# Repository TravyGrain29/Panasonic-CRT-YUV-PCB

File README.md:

# Panasonic-CRT-YUV-PCB
## DISCLAIMER
I'm not a professional, this was a side project I completed for fun. I cannot guarantee compatibility with your model CRT. I am not responsible for any damage or harm you may inflict upon yourself or your devices. Working on CRTs is very dangerous and should only be done by individuals with the required knowledge and experience. Do not attempt this project if you are a novice with electronics or CRTs.

## Overview

### CRT Specs
Model: Panasonic Tau TC-21PM50A

Chassis: GP3

UOC IC/Jungle: TDA9590N48AX

### What is this?
This is a PCB I designed, based off exisiting Panasonic schematics, that allows Panasonic Tau CRTs using the GP3 chassis to accept component (YPbPr) video input. This is intended for use with GP3 CRTs that lack native component or RGB inputs. The board converts incoming YPbPr signals from an external device into sigals that the video processor can understand and display properly. Without this PCB, the video will not display correctly and will appear distorted.

### How does it work?
Panasonic CRTs that utilise the GP3 chassis but lack component input, still have the basic foundations present that allow us to provide our own component input. This is due to Panasonic reusing the same chassis and processors between higher end and lower end models. All that was required for this mod was to unlock component input as an AV option via the service menu and then installing the missing hardware and connections. This board replaces the missing YUV circuit board that came with component enabled models, allowing us to build the YUV input path ourselves.

### How can I build this?
A written guide will be provided in PDF format with instructions on how to perform the modification.

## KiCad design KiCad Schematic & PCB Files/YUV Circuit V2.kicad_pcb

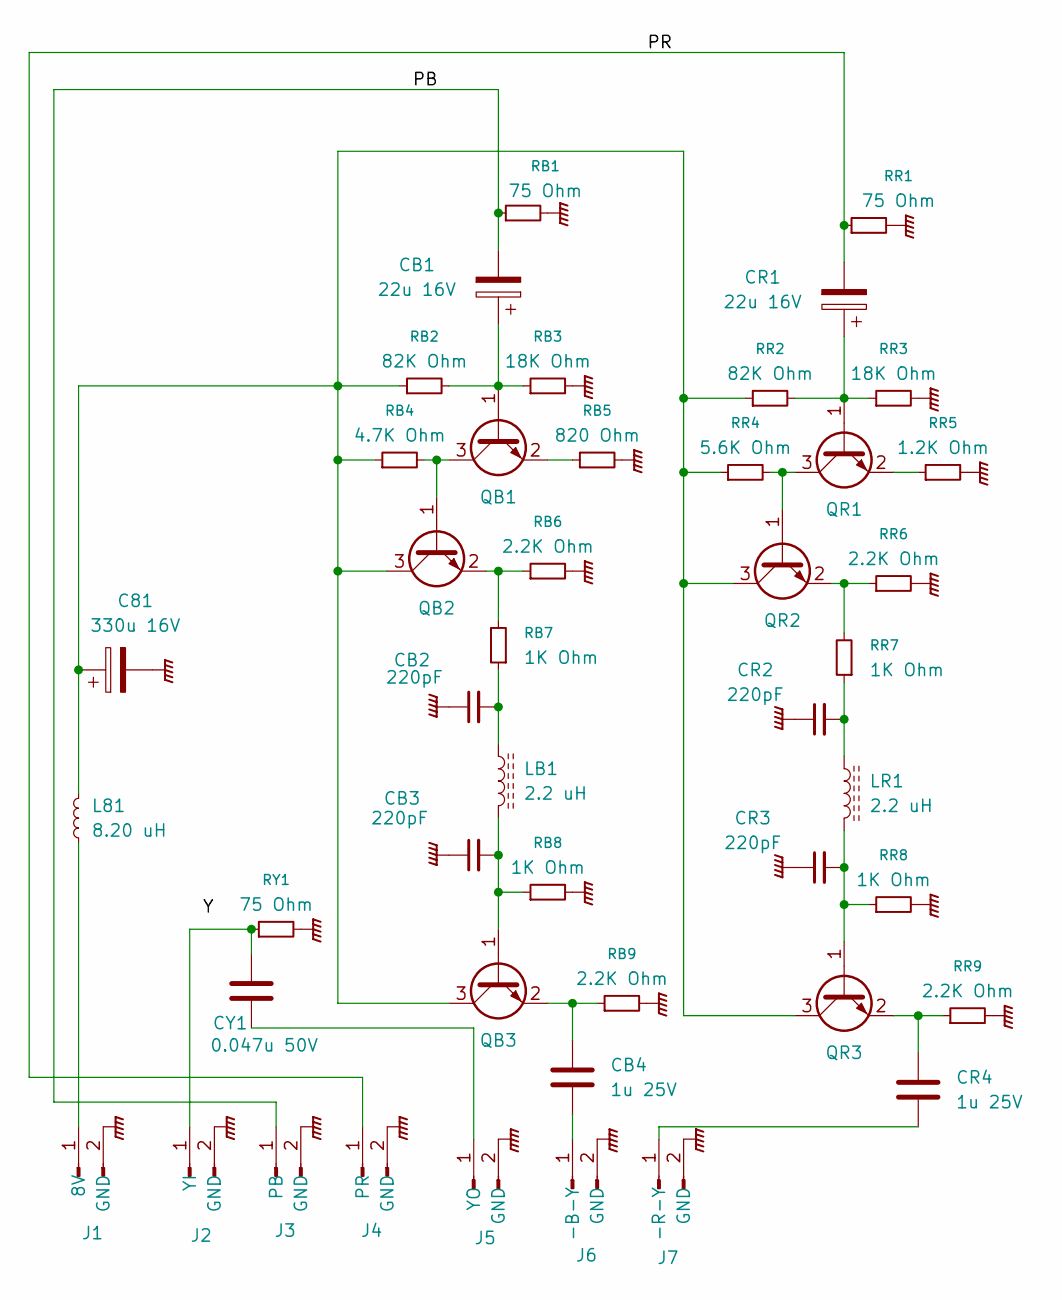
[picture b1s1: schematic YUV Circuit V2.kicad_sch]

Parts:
C81: 330u 16V; CP_Radial_D12.5mm_P5.00mm
CB1: 22u 16V; C_2220_5750Metric_Pad1.97x5.40mm_HandSolder
CB2, CB3: 220pF; C_0805_2012Metric_Pad1.18x1.45mm_HandSolder
CB4: 1u 25V; C_0805_2012Metric_Pad1.18x1.45mm_HandSolder
CR1: 22u 16V; C_2220_5750Metric_Pad1.97x5.40mm_HandSolder
CR2, CR3: 220pF; C_0805_2012Metric_Pad1.18x1.45mm_HandSolder
CR4: 1u 25V; C_0805_2012Metric_Pad1.18x1.45mm_HandSolder
CY1: 0.047u 50V; C_1206_3216Metric_Pad1.33x1.80mm_HandSolder
J1, J2, J3, J4, J5, J6, J7: Conn_01x02_Pin; JST_EH_B2B-EH-A_1x02_P2.50mm_Vertical
L81: 8.20 uH; L_Coilcraft_LPS3010
LB1: 2.2 uH; L_1008_2520Metric_Pad1.43x2.20mm_HandSolder
LR1: 2.2 uH; L_1008_2520Metric_Pad1.43x2.20mm_HandSolder
QB1: SOT-23-3
QB2, QB3: Q_NPN; SOT-23-3
QR1: SOT-23-3
QR2, QR3: Q_NPN; SOT-23-3
RB1: 75 Ohm; R_0805_2012Metric_Pad1.20x1.40mm_HandSolder
RB2: 82K Ohm; R_0805_2012Metric_Pad1.20x1.40mm_HandSolder
RB3: 18K Ohm; R_0805_2012Metric_Pad1.20x1.40mm_HandSolder
RB4: 4.7K Ohm; R_0805_2012Metric_Pad1.20x1.40mm_HandSolder
RB5: 820 Ohm; R_0805_2012Metric_Pad1.20x1.40mm_HandSolder
RB6, RB9: 2.2K Ohm; R_0805_2012Metric_Pad1.20x1.40mm_HandSolder
RB7, RB8: 1K Ohm; R_0805_2012Metric_Pad1.20x1.40mm_HandSolder
RR1: 75 Ohm; R_0805_2012Metric_Pad1.20x1.40mm_HandSolder
RR2: 82K Ohm; C_0805_2012Metric_Pad1.18x1.45mm_HandSolder
RR3: 18K Ohm; R_0805_2012Metric_Pad1.20x1.40mm_HandSolder
RR4: 5.6K Ohm; R_0805_2012Metric_Pad1.20x1.40mm_HandSolder
RR5: 1.2K Ohm; R_0805_2012Metric_Pad1.20x1.40mm_HandSolder
RR6, RR9: 2.2K Ohm; R_0805_2012Metric_Pad1.20x1.40mm_HandSolder
RR7, RR8: 1K Ohm; R_0805_2012Metric_Pad1.20x1.40mm_HandSolder
RY1: 75 Ohm; R_0805_2012Metric_Pad1.20x1.40mm_HandSolder

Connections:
/PB: CB1.2, J3.1 (PB), RB1.1
/PR: CR1.2, J4.1 (PR), RR1.1
GNDPWR: C81.2, CB2.1, CB3.1, CR2.1, CR3.1, J1.2 (GND), J2.2 (GND), J3.2 (GND), J4.2 (GND), J5.2 (GND), J6.2 (GND), J7.2 (GND), RB1.2, RB3.2, RB5.2, RB6.2, RB8.2, RB9.2, RR1.2, RR3.2, RR5.2, RR6.2, RR8.2, RR9.2, RY1.2
unnamed: CB2.2, LB1.1, RB7.1
unnamed: CR2.2, LR1.1, RR7.1
unnamed: J1.1 (8V), L81.1
unnamed: CY1.1, J2.1 (YI), RY1.1
unnamed: CY1.2, J5.1 (YO)
unnamed: CB4.2, J6.1 (-B-Y)
unnamed: CR4.2, J7.1 (-R-Y)
unnamed: CB1.1, QB1.1 (B), RB2.2, RB3.1
unnamed: QB1.3 (C), QB2.1 (B), RB4.2
unnamed: QB1.2 (E), RB5.1
unnamed: C81.1, L81.2, QB2.3 (C), QB3.3 (C), QR2.3 (C), QR3.3 (C), RB2.1, RB4.1, RR2.1, RR4.1
unnamed: QB2.2 (E), RB6.1, RB7.2
unnamed: CB3.2, LB1.2, QB3.1 (B), RB8.1
unnamed: CB4.1, QB3.2 (E), RB9.1
unnamed: CR1.1, QR1.1 (B), RR2.2, RR3.1
unnamed: QR1.3 (C), QR2.1 (B), RR4.2
unnamed: QR1.2 (E), RR5.1
unnamed: QR2.2 (E), RR6.1, RR7.2
unnamed: CR3.2, LR1.2, QR3.1 (B), RR8.1
unnamed: CR4.1, QR3.2 (E), RR9.1

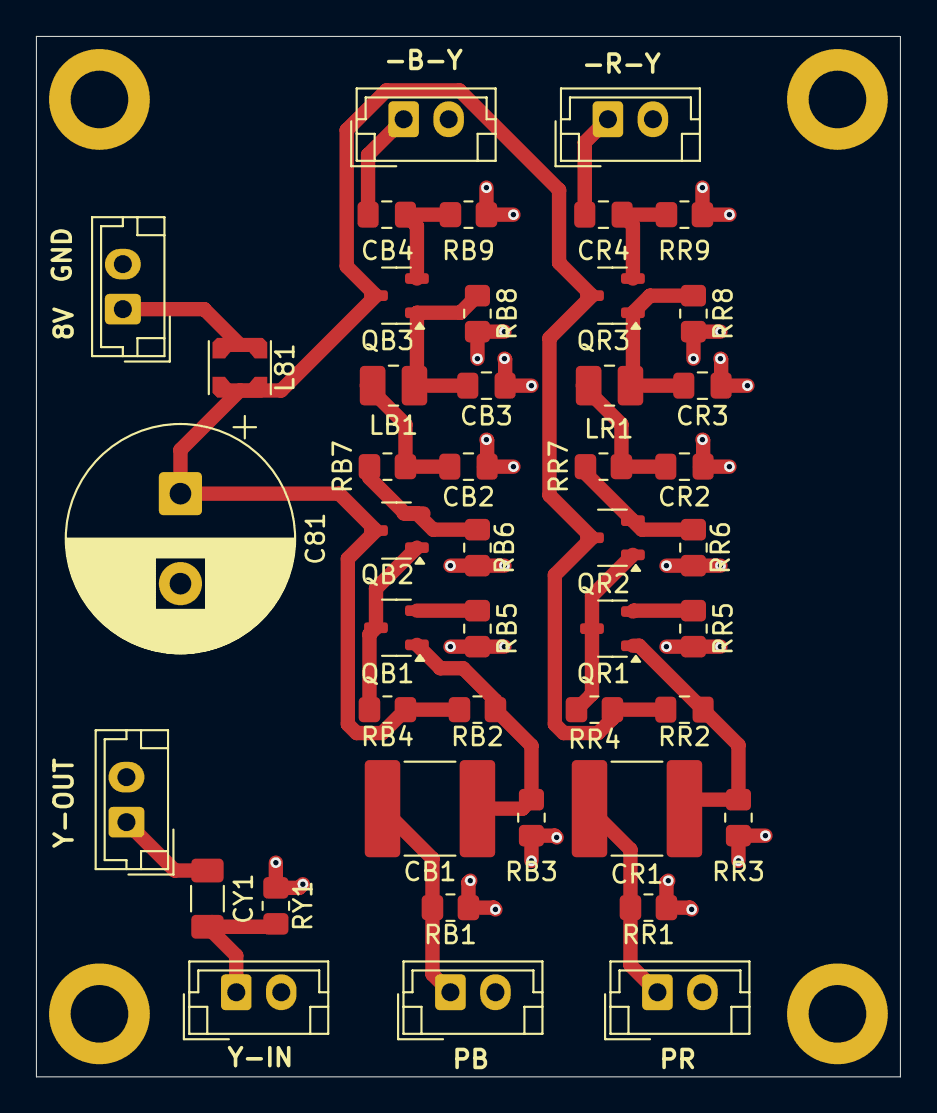
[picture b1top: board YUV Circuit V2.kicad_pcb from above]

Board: 2 copper layers, 48.0 x 57.8 mm, 45 parts (0 on the bottom side), 23 nets.
